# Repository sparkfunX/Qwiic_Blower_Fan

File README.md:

Qwiic Blower Fan
========================================

[

[*Qwiic Blower Fan (SPX-18561)*](https://www.sparkfun.com/products/18561)

The unmistakable sounds of a tiny cooling fan spooling up usually means you've sat your laptop on a soft surface, or launched one too many tabs in your browser. It's a textbook cry for help from all of our favorite consumer electronics but what if your next hardware project could also complain about overheating? Well now it can!

In all seriousness, though, sometimes you need to move a little air around. Whether for active cooling or ventilation, a tiny fan can make a big difference. However, a tiny fan also has tiny wires which can make it difficult to work with. We've remedied this issue by mounting it to a board along with the mating flat-flex connector, a voltage booster and an ATtiny-based driver so you can power and control the fan over the Qwiic bus.

The control firmware monitors the tachometer output of the fan in order to implement PI Control over the fan speed, allowing you to set your desired speed in real units. It's also possible to disable the PI control loop and set the speed as a proportion of the maximum. The accompanying Arduino library includes example code for controlling the fan, tweaking settings, and even setting the fan speed based on an attached Qwiic Temperature Sensor and a lookup table.

We're unable to find a datasheet for this fan in particular (which is intended to replace the OEM fan in a Nintendo Switch)

Heads Up! This device draws enough power that it operates at the upper limit of the Qwiic bus. If there are few other devices on the bus and the fan is not allowed to rapidly change throttle, it is possible to power this fan directly from the bus. In some applications, however, it may be necessary to provide the blower fan with a dedicated 3.3V supply.

Repository Contents
-------------------

* **/Firmware** - Control firmware for the ATtiny
* **/Hardware** - Eagle design files (.brd, .sch)
* **/Production** - Panelized hardware files for production

License Information
-------------------

This product is _**open source**_! 

Please review the LICENSE.md file for license information. 

If you have any questions or concerns on licensing, please contact technical support on our [SparkFun forums](https://forum.sparkfun.com/viewforum.php?f=152).

Distributed as-is; no warranty is given.

- Your friends at SparkFun.

_<COLLABORATION CREDIT>_

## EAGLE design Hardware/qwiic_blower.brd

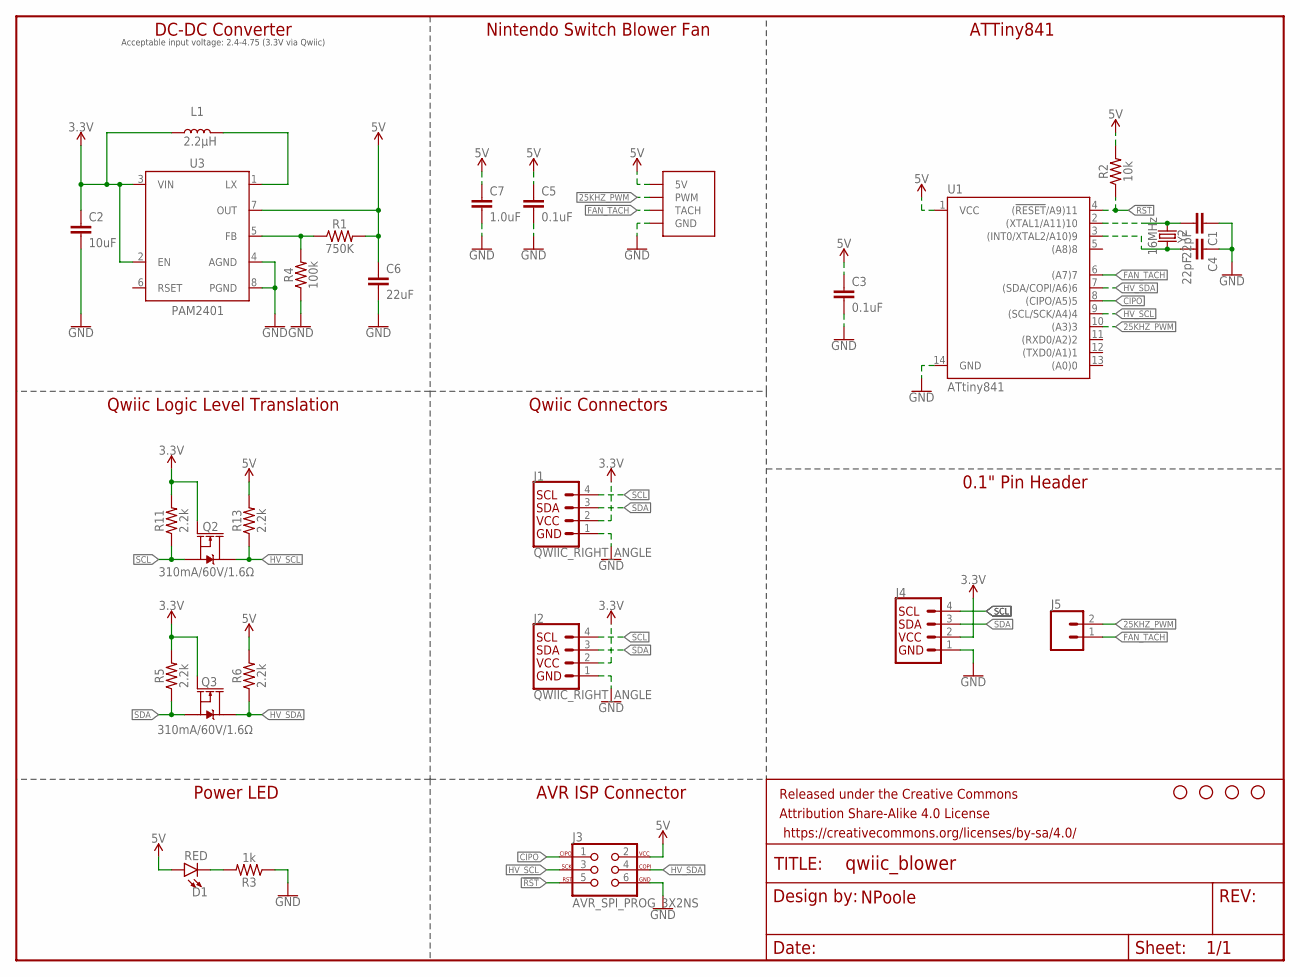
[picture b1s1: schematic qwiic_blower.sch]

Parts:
C1, C4: 22pF; 0603
C2: 10uF; 0603
C3, C5: 0.1uF; 0603
C6: 22uF; 0805
C7: 1.0uF; 0603
D1: RED; LED-0603
FRAME1: FRAME-LETTER; CREATIVE_COMMONS
H1, H2, H3, H4: STAND-OFF
J1, J2: QWIIC_RIGHT_ANGLE; JST04_1MM_RA
J3: AVR_SPI_PROG_3X2NS; 2X3-NS
J4: I2C_STANDARD_NO_SILK; 1X04_NO_SILK
J5: CONN_021X02_NO_SILK; 1X02_NO_SILK
L1: 2.2μH; 0806
Q2, Q3: 310mA/60V/1.6Ω; SOT323
R1: 750K; 0603
R2: 10k; 0603
R3: 1k; 0603
R4: 100k; 0603
R5, R6, R11, R13: 2.2k; 0603
U1: ATtiny841; SO14
U3: PAM2401; MSOP8
U$19: NINTENDO_SWITCH_FAN; FPC_4_0.5MM
Y2: 16MHz; CRYSTAL-SMD-2.0X1.6MM

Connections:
3.3V: C2.1, J1.2, J2.2, J4.2, L1.1, Q2.1 (G), Q3.1 (G), R5.2, R11.2, U3.2 (EN), U3.3 (VIN)
5V: C3.1, C5.1, C6.1, C7.1, D1.A, J3.2, R1.2, R2.2, R6.2, R13.2, U1.1 (VCC), U3.7 (OUT), U$19.1 (5V)
25KHZ_PWM: J5.2, U1.10 ((A3)3), U$19.4 (PWM)
!RST: J3.5, R2.1, U1.4 ((!RESET!/A9)11)
CIPO: J3.1, U1.8 ((CIPO/A5)5)
FAN_TACH: J5.1, U1.6 ((A7)7), U$19.2 (TACH)
GND: C1.1, C2.2, C3.2, C4.1, C5.2, C6.2, C7.2, J1.1, J2.1, J3.6, J4.1, R3.1, R4.1, U1.14 (GND), U3.4 (AGND), U3.8 (PGND), U$19.3 (GND)
HV_SCL: J3.3, Q2.3 (D), R13.1, U1.9 ((SCL/SCK/A4)4)
HV_SDA: J3.4, Q3.3 (D), R6.1, U1.7 ((SDA/COPI/A6)6)
unnamed: C4.2, U1.3 ((INT0/XTAL2/A10)9), Y2.1
unnamed: R1.1, R4.2, U3.5 (FB)
unnamed: L1.2, U3.1 (LX)
unnamed: C1.2, U1.2 ((XTAL1/A11)10), Y2.3 (2)
unnamed: D1.C, R3.2
SCL: J1.4, J2.4, J4.4, Q2.2 (S), R11.1
SDA: J1.3, J2.3, J4.3, Q3.2 (S), R5.1

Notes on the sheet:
DC-DC Converter
Acceptable input voltage: 2.4-4.75 (3.3V via Qwiic)
Nintendo Switch Blower Fan
ATTiny841
Qwiic Connectors
Qwiic Logic Level Translation
0.1" Pin Header
AVR ISP Connector
Power LED
NPoole

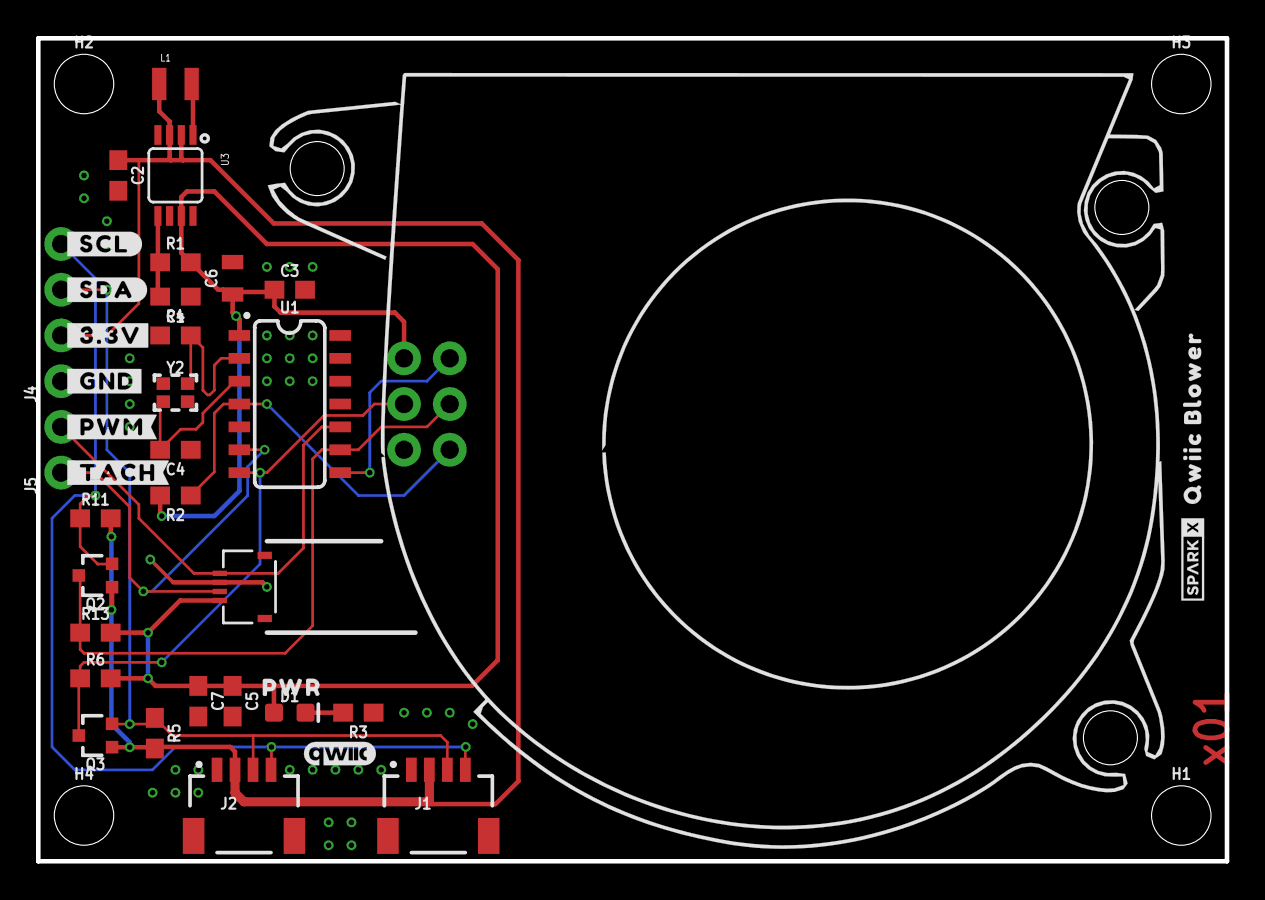
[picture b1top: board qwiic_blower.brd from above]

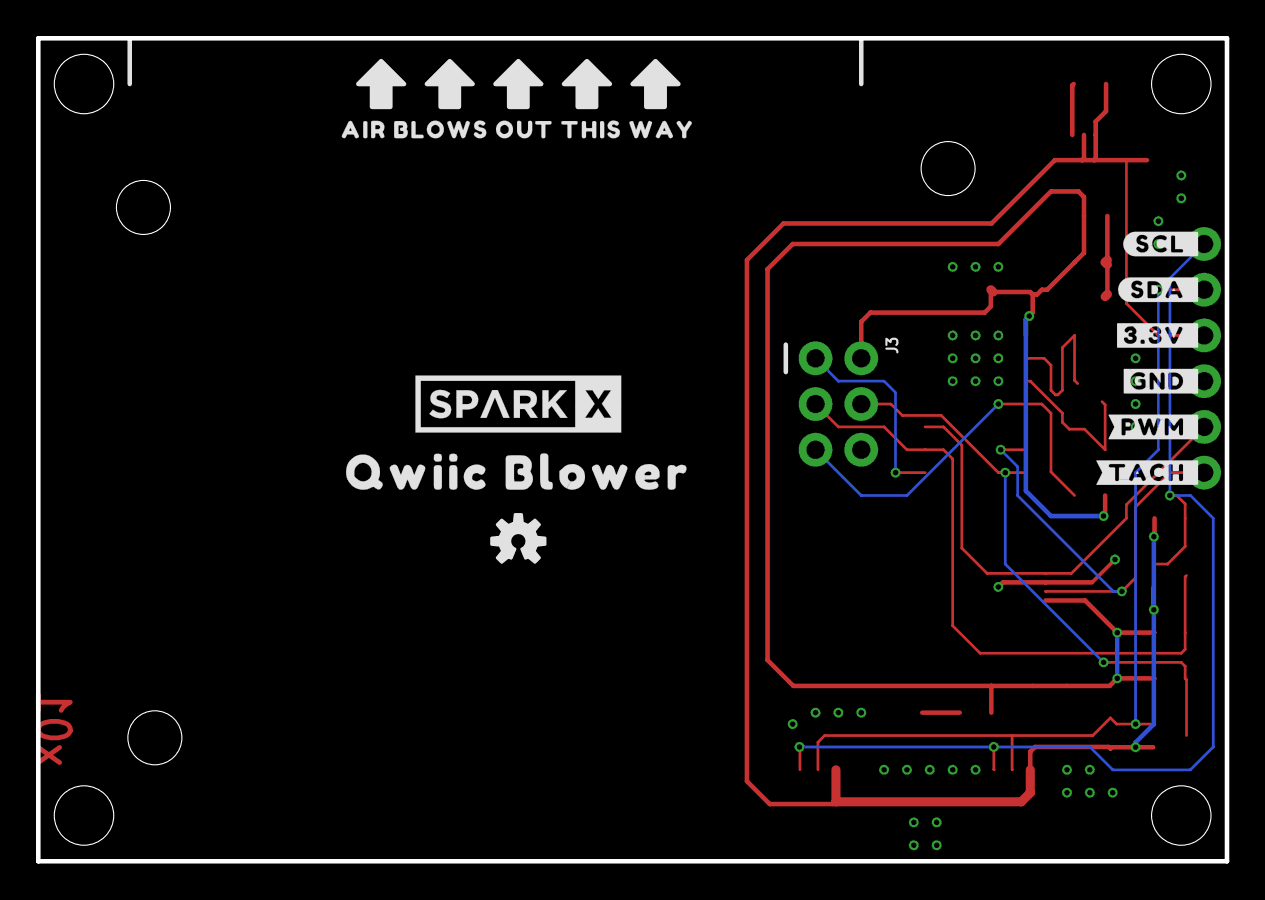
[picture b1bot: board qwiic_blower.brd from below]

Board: 2 copper layers, 66.0 x 45.7 mm, 53 parts (11 on the bottom side), 16 nets.

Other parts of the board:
U$1: #_TACH#0
U$2: #_PWM#0
U$3: #_GND#0
U$4: #_3#3V#0
U$5: #_SDA#0
U$6: #_SCL#0
U$7: #SCL_#0
U$8: #SDA_#0
U$9: #3#3V_#0
U$10: #GND_#0
U$11: #PWM_#0
U$12: #TACH_#0
U$13: QWIIC_4MM
U$14: QWIIC_BLOWER0
U$15: SPARKX-TINY
U$16: AIR_BLOWS_OUT_THIS_WAY0
U$17: _QWIIC_BLOWER_0
U$18: SPARKX-LARGE
U$20: OSHW-LOGO-S
U$21: PWR0

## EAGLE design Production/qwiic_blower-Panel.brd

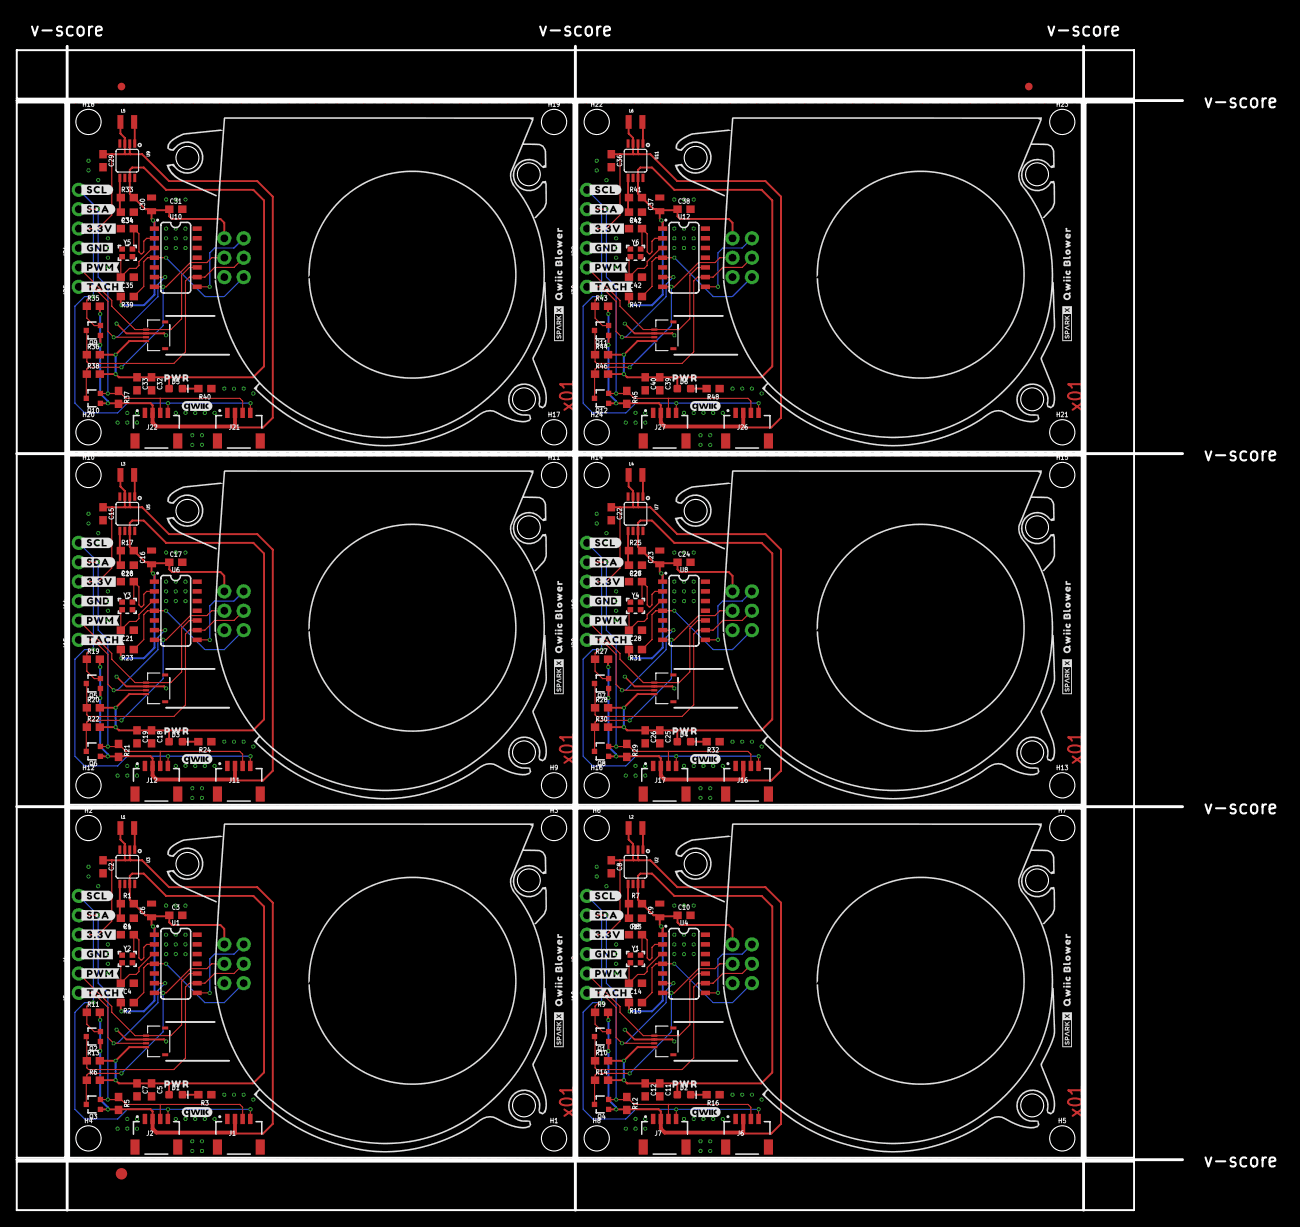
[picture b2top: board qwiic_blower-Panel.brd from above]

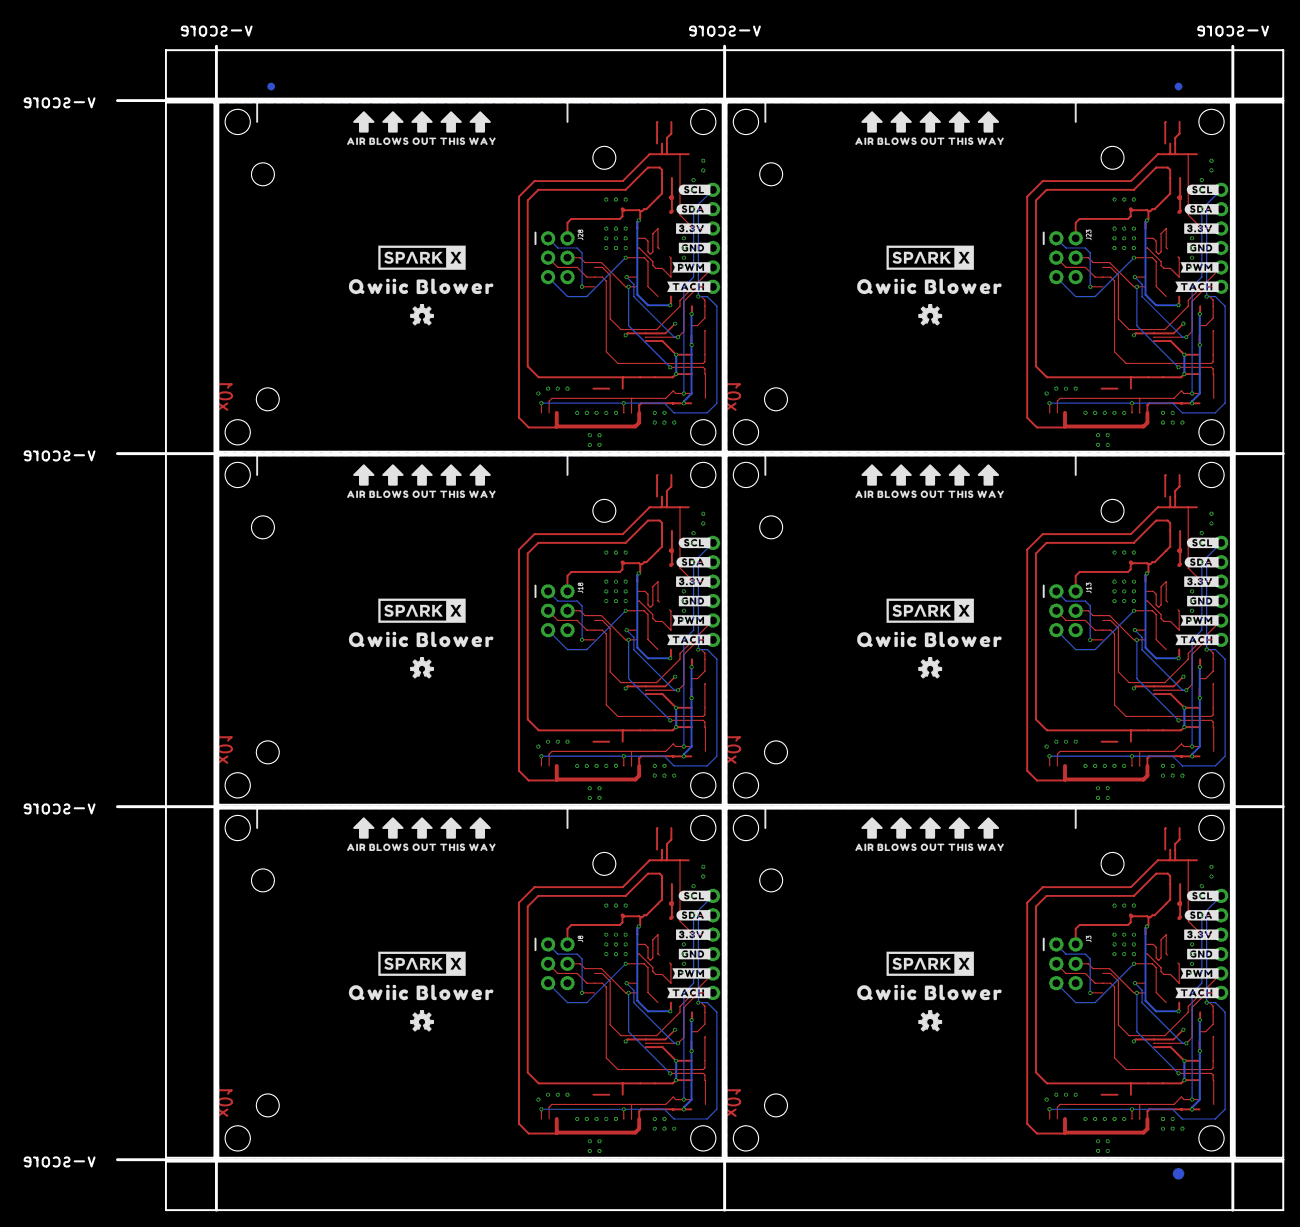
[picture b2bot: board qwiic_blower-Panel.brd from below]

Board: 2 copper layers, 165.8 x 156.3 mm, 318 parts (69 on the bottom side), 96 nets.

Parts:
C1, C4, C13, C14, C20, C21, C27, C28, C34, C35, C41, C42: 22pF; 0603
C2, C8, C15, C22, C29, C36: 10uF; 0603
C3, C5, C10, C11, C17, C18, C24, C25, C31, C32, C38, C39: 0.1uF; 0603
C6, C9, C16, C23, C30, C37: 22uF; 0805
C7, C12, C19, C26, C33, C40: 1.0uF; 0603
D1, D2, D3, D4, D5, D6: RED; LED-0603
E$1, E$2, E$3, E$4: FIDUCIAL-1X2
E$5, E$6: FIDUCIAL-1.5X3
H1, H2, H3, H4, H5, H6, H7, H8, H9, H10, H11, H12, H13, H14, H15, H16, H17, H18, H19, H20, H21, H22, H23, H24: STAND-OFF
J1, J2, J6, J7, J11, J12, J16, J17, J21, J22, J26, J27: QWIIC_RIGHT_ANGLE; JST04_1MM_RA
J3, J8, J13, J18, J23, J28: AVR_SPI_PROG_3X2NS; 2X3-NS
J4, J9, J14, J19, J24, J29: 1X04_NO_SILK
J5, J10, J15, J20, J25, J30: 1X02_NO_SILK
L1, L2, L3, L4, L5, L6: 2.2μH; 0806
Q1, Q2, Q3, Q4, Q5, Q6, Q7, Q8, Q9, Q10, Q11, Q12: 310mA/60V/1.6Ω; SOT323
R1, R7, R17, R25, R33, R41: 750K; 0603
R2, R15, R23, R31, R39, R47: 10k; 0603
R3, R16, R24, R32, R40, R48: 1k; 0603
R4, R8, R18, R26, R34, R42: 100k; 0603
R5, R6, R9, R10, R11, R12, R13, R14, R19, R20, R21, R22, R27, R28, R29, R30, R35, R36, R37, R38, R43, R44, R45, R46: 2.2k; 0603
U1, U4, U6, U8, U10, U12: ATtiny841; SO14
U2, U3, U5, U7, U9, U11: PAM2401; MSOP8
U$1, U$22, U$43, U$64, U$85, U$106: #_TACH#0
U$2, U$23, U$44, U$65, U$86, U$107: #_PWM#0
U$3, U$24, U$45, U$66, U$87, U$108: #_GND#0
U$4, U$25, U$46, U$67, U$88, U$109: #_3#3V#0
U$5, U$26, U$47, U$68, U$89, U$110: #_SDA#0
U$6, U$27, U$48, U$69, U$90, U$111: #_SCL#0
U$7, U$28, U$49, U$70, U$91, U$112: #SCL_#0
U$8, U$29, U$50, U$71, U$92, U$113: #SDA_#0
U$9, U$30, U$51, U$72, U$93, U$114: #3#3V_#0
U$10, U$31, U$52, U$73, U$94, U$115: #GND_#0
U$11, U$32, U$53, U$74, U$95, U$116: #PWM_#0
U$12, U$33, U$54, U$75, U$96, U$117: #TACH_#0
U$13, U$34, U$55, U$76, U$97, U$118: QWIIC_4MM
U$14, U$35, U$56, U$77, U$98, U$119: QWIIC_BLOWER0
U$15, U$36, U$57, U$78, U$99, U$120: SPARKX-TINY
U$16, U$37, U$58, U$79, U$100, U$121: AIR_BLOWS_OUT_THIS_WAY0
U$17, U$38, U$59, U$80, U$101, U$122: _QWIIC_BLOWER_0
U$18, U$39, U$60, U$81, U$102, U$123: SPARKX-LARGE
U$19, U$40, U$61, U$82, U$103, U$124: NINTENDO_SWITCH_FAN; FPC_4_0.5MM
U$20, U$41, U$62, U$83, U$104, U$125: OSHW-LOGO-S
U$21, U$42, U$63, U$84, U$105, U$126: PWR0
Y1, Y2, Y3, Y4, Y5, Y6: 16MHz; CRYSTAL-SMD-2.0X1.6MM

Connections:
3.3V: C2.1, J1.2, J2.2, J4.2, L1.1, Q2.1, Q3.1, R5.2, R11.2, U3.2, U3.3
3.3V1: C8.1, J6.2, J7.2, J9.2, L2.1, Q1.1, Q4.1, R9.2, R12.2, U2.2, U2.3
3.3V2: C15.1, J11.2, J12.2, J14.2, L3.1, Q5.1, Q6.1, R19.2, R21.2, U5.2, U5.3
3.3V3: C22.1, J16.2, J17.2, J19.2, L4.1, Q7.1, Q8.1, R27.2, R29.2, U7.2, U7.3
3.3V4: C29.1, J21.2, J22.2, J24.2, L5.1, Q9.1, Q10.1, R35.2, R37.2, U9.2, U9.3
3.3V5: C36.1, J26.2, J27.2, J29.2, L6.1, Q11.1, Q12.1, R43.2, R45.2, U11.2, U11.3
5V: C3.1, C5.1, C6.1, C7.1, D1.A, J3.2, R1.2, R2.2, R6.2, R13.2, U1.1, U3.7, U$19.1
5V1: C9.1, C10.1, C11.1, C12.1, D2.A, J8.2, R7.2, R10.2, R14.2, R15.2, U2.7, U4.1, U$40.1
5V2: C16.1, C17.1, C18.1, C19.1, D3.A, J13.2, R17.2, R20.2, R22.2, R23.2, U5.7, U6.1, U$61.1
5V3: C23.1, C24.1, C25.1, C26.1, D4.A, J18.2, R25.2, R28.2, R30.2, R31.2, U7.7, U8.1, U$82.1
5V4: C30.1, C31.1, C32.1, C33.1, D5.A, J23.2, R33.2, R36.2, R38.2, R39.2, U9.7, U10.1, U$103.1
5V5: C37.1, C38.1, C39.1, C40.1, D6.A, J28.2, R41.2, R44.2, R46.2, R47.2, U11.7, U12.1, U$124.1
25KHZ_PWM: J5.2, U1.10, U$19.4
25KHZ_PWM1: J10.2, U4.10, U$40.4
25KHZ_PWM2: J15.2, U6.10, U$61.4
25KHZ_PWM3: J20.2, U8.10, U$82.4
25KHZ_PWM4: J25.2, U10.10, U$103.4
25KHZ_PWM5: J30.2, U12.10, U$124.4
!RST: J3.5, R2.1, U1.4
!RST1: J8.5, R15.1, U4.4
!RST2: J13.5, R23.1, U6.4
!RST3: J18.5, R31.1, U8.4
!RST4: J23.5, R39.1, U10.4
!RST5: J28.5, R47.1, U12.4
CIPO: J3.1, U1.8
CIPO1: J8.1, U4.8
CIPO2: J13.1, U6.8
CIPO3: J18.1, U8.8
CIPO4: J23.1, U10.8
CIPO5: J28.1, U12.8
FAN_TACH: J5.1, U1.6, U$19.2
FAN_TACH1: J10.1, U4.6, U$40.2
FAN_TACH2: J15.1, U6.6, U$61.2
FAN_TACH3: J20.1, U8.6, U$82.2
FAN_TACH4: J25.1, U10.6, U$103.2
FAN_TACH5: J30.1, U12.6, U$124.2
GND: C1.1, C2.2, C3.2, C4.1, C5.2, C6.2, C7.2, J1.1, J2.1, J3.6, J4.1, R3.1, R4.1, U1.14, U3.4, U3.8, U$19.3
GND1: C8.2, C9.2, C10.2, C11.2, C12.2, C13.1, C14.1, J6.1, J7.1, J8.6, J9.1, R8.1, R16.1, U2.4, U2.8, U4.14, U$40.3
GND2: C15.2, C16.2, C17.2, C18.2, C19.2, C20.1, C21.1, J11.1, J12.1, J13.6, J14.1, R18.1, R24.1, U5.4, U5.8, U6.14, U$61.3
GND3: C22.2, C23.2, C24.2, C25.2, C26.2, C27.1, C28.1, J16.1, J17.1, J18.6, J19.1, R26.1, R32.1, U7.4, U7.8, U8.14, U$82.3
GND4: C29.2, C30.2, C31.2, C32.2, C33.2, C34.1, C35.1, J21.1, J22.1, J23.6, J24.1, R34.1, R40.1, U9.4, U9.8, U10.14, U$103.3
GND5: C36.2, C37.2, C38.2, C39.2, C40.2, C41.1, C42.1, J26.1, J27.1, J28.6, J29.1, R42.1, R48.1, U11.4, U11.8, U12.14, U$124.3
HV_SCL: J3.3, Q2.3, R13.1, U1.9
HV_SCL1: J8.3, Q1.3, R10.1, U4.9
HV_SCL2: J13.3, Q5.3, R20.1, U6.9
HV_SCL3: J18.3, Q7.3, R28.1, U8.9
HV_SCL4: J23.3, Q9.3, R36.1, U10.9
HV_SCL5: J28.3, Q11.3, R44.1, U12.9
HV_SDA: J3.4, Q3.3, R6.1, U1.7
HV_SDA1: J8.4, Q4.3, R14.1, U4.7
HV_SDA2: J13.4, Q6.3, R22.1, U6.7
HV_SDA3: J18.4, Q8.3, R30.1, U8.7
HV_SDA4: J23.4, Q10.3, R38.1, U10.7
HV_SDA5: J28.4, Q12.3, R46.1, U12.7
unnamed: C4.2, U1.3, Y2.1
unnamed: R1.1, R4.2, U3.5
unnamed: L1.2, U3.1
unnamed: C1.2, U1.2, Y2.3
unnamed: D1.C, R3.2
unnamed: R7.1, R8.2, U2.5
unnamed: L2.2, U2.1
unnamed: C14.2, U4.3, Y1.1
unnamed: C13.2, U4.2, Y1.3
unnamed: D2.C, R16.2
unnamed: R17.1, R18.2, U5.5
unnamed: L3.2, U5.1
unnamed: C21.2, U6.3, Y3.1
unnamed: C20.2, U6.2, Y3.3
unnamed: D3.C, R24.2
unnamed: R25.1, R26.2, U7.5
unnamed: L4.2, U7.1
unnamed: C28.2, U8.3, Y4.1
unnamed: C27.2, U8.2, Y4.3
unnamed: D4.C, R32.2
unnamed: R33.1, R34.2, U9.5
unnamed: L5.2, U9.1
unnamed: C35.2, U10.3, Y5.1
unnamed: C34.2, U10.2, Y5.3
unnamed: D5.C, R40.2
unnamed: R41.1, R42.2, U11.5
unnamed: L6.2, U11.1
unnamed: C42.2, U12.3, Y6.1
unnamed: C41.2, U12.2, Y6.3
unnamed: D6.C, R48.2
SCL: J1.4, J2.4, J4.4, Q2.2, R11.1
SCL1: J6.4, J7.4, J9.4, Q1.2, R9.1
SCL2: J11.4, J12.4, J14.4, Q5.2, R19.1
SCL3: J16.4, J17.4, J19.4, Q7.2, R27.1
SCL4: J21.4, J22.4, J24.4, Q9.2, R35.1
SCL5: J26.4, J27.4, J29.4, Q11.2, R43.1
SDA: J1.3, J2.3, J4.3, Q3.2, R5.1
SDA1: J6.3, J7.3, J9.3, Q4.2, R12.1
SDA2: J11.3, J12.3, J14.3, Q6.2, R21.1
SDA3: J16.3, J17.3, J19.3, Q8.2, R29.1
SDA4: J21.3, J22.3, J24.3, Q10.2, R37.1
SDA5: J26.3, J27.3, J29.3, Q12.2, R45.1

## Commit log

2021-07-19 x01 PCBs ordered
2021-12-06 V1 Docs and Housecleaning
2022-01-09 Firmware v11
    Firmware update to address bugs filed by dlkeng
    - Enforce basic I2C Address validity
    - readTachometer() now returns 0 if asked to divide by 0 (instead of attempting it and crashing)
    - requestEvent() now writes all registers to the buffer starting at the requested index and ending at sizeof(registerMap) so it cannot run away
    - receiveEvent() now wraps incoming bytes when reaching the end of the register map
    - Add firmware version register (reports version 11)
2022-01-12 Add "Programming" directory
    - batch_program.bat will correctly program the fuse bits and flash using an attached AVR Pocket Programmer
2022-01-12 Update batch_program.bat
    - changed fuse bits to set the brownout detection to 2.7v

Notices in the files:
parts and their libraries:
SparkFun-Aesthetics: Licensing: Creative Commons ShareAlike 4.0 International - https://creativecommons.org/licenses/by-sa/4.0
SparkFun-Aesthetics: Released under the Creative Commons Attribution Share-Alike 4.0 License
SparkFun-Aesthetics: https://creativecommons.org/licenses/by-sa/4.0
